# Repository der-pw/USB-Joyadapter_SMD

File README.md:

# USB-Joyadapter_SMD  
ATtiny basierter USB adapter für classic DB9 joysticks.

Die Ursprungsidee kommt aus dem forum64.de.  
https://www.forum64.de/index.php?thread/43055-usb-joystickadapter-neue-firmware-weiterentwicklung/

Die Software ist frei verfügbar und wird u.a. in dem [Thread](https://www.forum64.de/index.php?thread/43055-usb-joystickadapter-neue-firmware-weiterentwicklung/&postID=1390222#post1390222) zum Download angeboten, alle anderen Quellen, zumindest die, die ich gefunden habe, laufen ins Leere.
Daher stelle ich die Daten, der Vollständigkeit halber in dem Ordner [USB-Joystickadapter_THT](https://github.com/der-pw/USB-Joyadapter_SMD/tree/main/USB-Joystickadapter_THT) mit zur Verfügung. Darin enthalten sind sowohl die Software, zwei kompillierte Versionen, einmal für ATtiny2313 und ATtiny4313 und zusätzlich auch die Boarddaten der "alten" THT-Version.  
Ich bin aber nicht der Author!

Ich wollte eine SMD Version, möglichst kompakt aber noch gut zum Handlöten, haben.
Das Platinenlayout liegt als [KiCad-Projekt](https://github.com/der-pw/USB-Joyadapter_SMD/tree/main/kicad) vor. Exportierte Gerberdaten für Fertiger (bspw. [JLCPCB](https://jlcpcb.com/)) kann man ebenfalls [hier herunterladen](https://github.com/der-pw/USB-Joyadapter_SMD/raw/main/Joyadapter_SMD_gerber.zip).

### Programmierung
Ich habe das Hexfile mittels [AVRDUDESS](https://github.com/zkemble/AVRDUDESS) und einem ISP-Programmer auf den ATtiny geschrieben.
Die ISP-Schnittstelle wurde aus Platzgründen als SMD-Pads ausgeführt.
Eine Möglichkeit, man lötet Verbindungskabel zum Programmer an, ober man baut mit einer Buchsenleiste 6x1 RM2,54, 6 Pogo-Pins (P50-B1) und dem [Adapter](https://github.com/der-pw/USB-Joyadapter_SMD/blob/main/3D%20print/Pogo-Adapter.stl) eine Programmierklemme.
Da man das Teil prinzipiell nur einmal flashed und die Software ist m.E. ausentwickelt, kann man wohl eher kurz ein paar Kabel anlöten.

Die Fuses habe ich folgendermaßen gesetzt.  
**Low:** *0xCF*  
**High:** *0xDB*  
**Ext:** *0xFF*  
Fusecalc: https://www.engbedded.com/fusecalc/

### Gehäuse
Es gibt auch ein Gehäuse in der Variante mit den hochstehenden DB9-Buchsen.  
Zum Festschrauben beider Gehäusehälften wurden 2x12mm Linsenkopfschrauben verwendet.

Alternativ könnte man auch 90° gewinkelte DB9-Buchsen verwenden. Dann gucken die Kabel rechts und links aus dem Gehäuse heraus.
Ich wollte es erst einmal recht kompakt haben.
Vielleicht ergibt sich nochmal die Gelegenheit für ein Gehäuse mit 90° Buchsen.

### Teileliste:
https://www.reichelt.de/my/1803950  
Einige Teile sind (Stand 06.21) schwer zu bekommen.  

Ein großer **Dank** geht an das [forum64.de](https://www.forum64.de/) und seine hilfsbereiten Mitglieder. :thumbsup:

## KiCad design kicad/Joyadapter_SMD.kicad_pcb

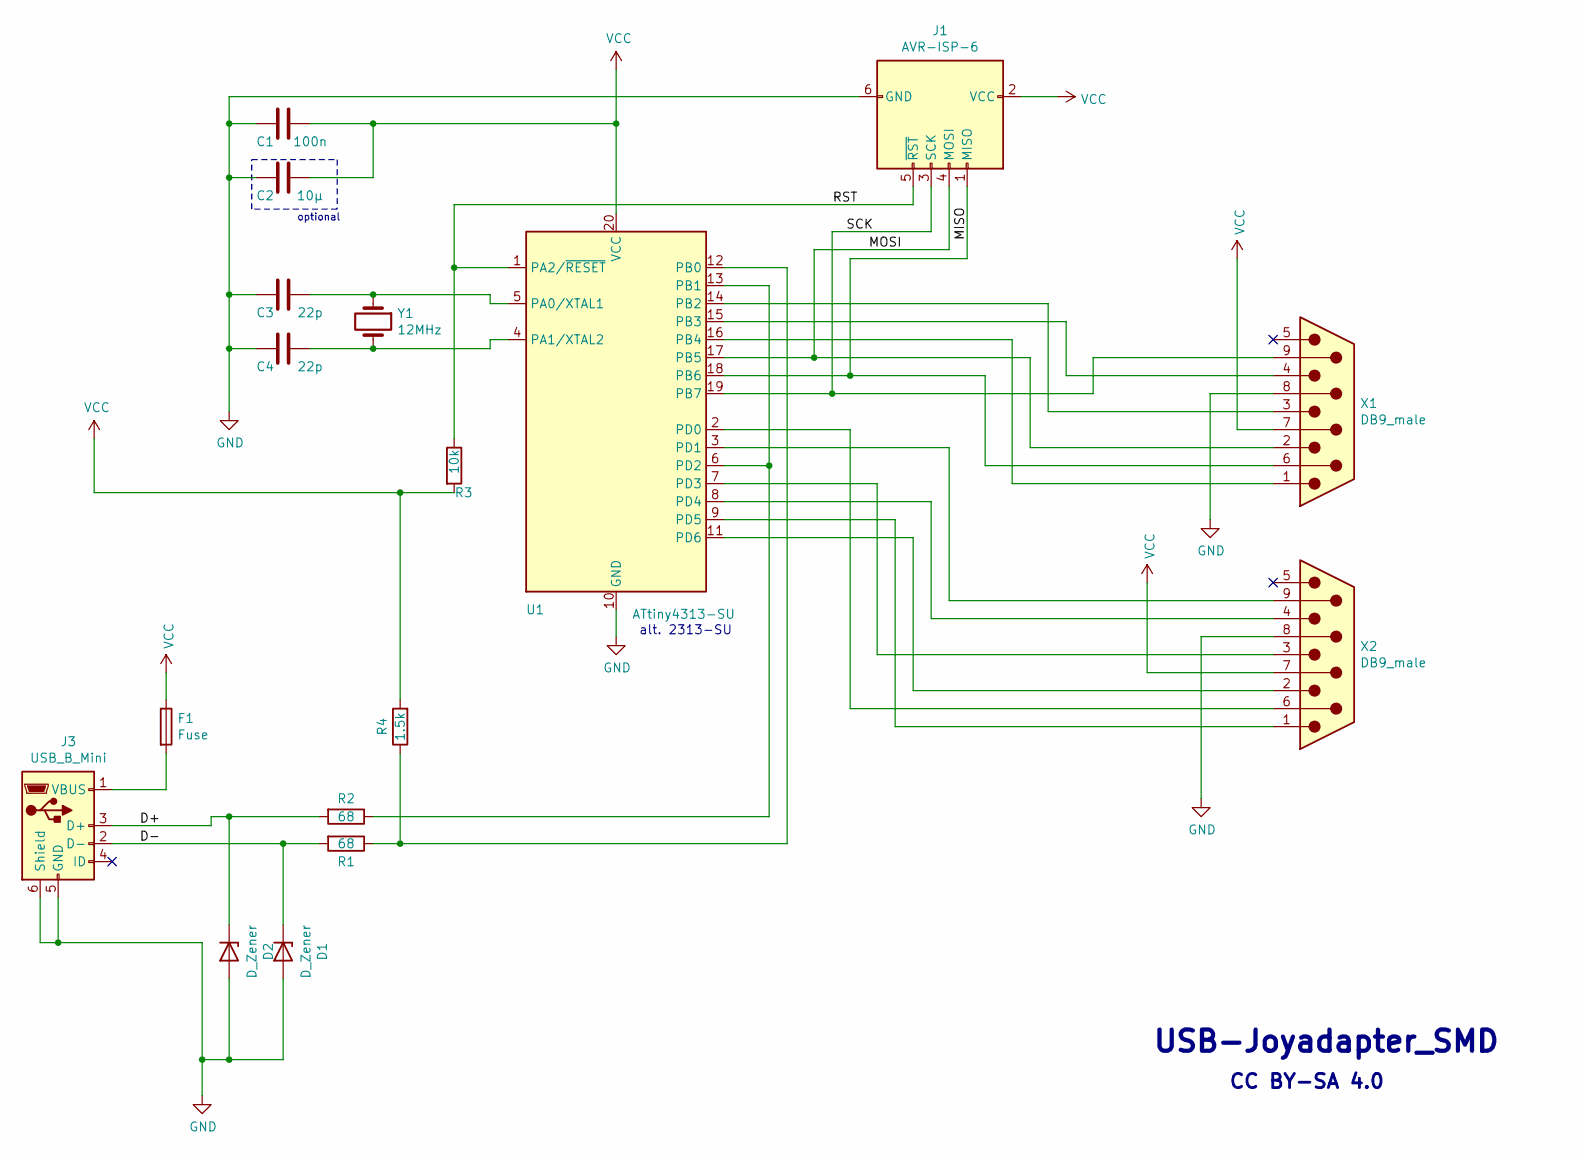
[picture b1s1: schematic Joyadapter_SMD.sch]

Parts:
C1: 100n; C_0805_2012Metric_Pad1.18x1.45mm_HandSolder
C2: 10µ; CP_EIA-3216-18_Kemet-A_Pad1.58x1.35mm_HandSolder
C3, C4: 22p; C_0805_2012Metric_Pad1.18x1.45mm_HandSolder
D1, D2: D_Zener; SOD-80
F1: Fuse; Fuse_0805_2012Metric_Pad1.15x1.40mm_HandSolder
J1: AVR-ISP-6; PinHeader_1x06_P2.54mm_Vertical
J3: USB_B_Mini; USB BWM USB-Einbaubuchse B-Mini
R1, R2: 68; R_0805_2012Metric_Pad1.20x1.40mm_HandSolder
R3: 10k; R_0805_2012Metric_Pad1.20x1.40mm_HandSolder
R4: 1.5k; R_0805_2012Metric_Pad1.20x1.40mm_HandSolder
U1: ATtiny4313-SU; SOIC-20W_7.5x12.8mm_P1.27mm
X1, X2: DB9_male; DSUB-9_Male_Vertical_P2.77x2.84mm_MountingHoles
Y1: 12MHz; HC49-SMD

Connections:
/D+: D2.1 (K), J3.3 (D+), R2.2
/D-: D1.1 (K), J3.2 (D-), R1.2
/MISO: J1.1 (MISO), U1.18 (PB6), X1.6
/MOSI: J1.4 (MOSI), U1.17 (PB5), X1.2
/RST: J1.5 (~RST), R3.1, U1.1 (PA2/~RESET)
/SCK: J1.3 (SCK), U1.19 (PB7), X1.9
GND: C1.2, C2.2, C3.2, C4.2, D1.2 (A), D2.2 (A), J1.6 (GND), J3.5 (GND), J3.6 (Shield), U1.10 (GND), X1.8, X2.8
unnamed: C3.1, U1.5 (PA0/XTAL1), Y1.1
unnamed: C4.1, U1.4 (PA1/XTAL2), Y1.2
unnamed: F1.2, J3.1 (VBUS)
unnamed: R1.1, R4.1, U1.12 (PB0)
unnamed: R2.1, U1.6 (PD2), U1.13 (PB1)
unnamed: U1.2 (PD0), X2.6
unnamed: U1.3 (PD1), X2.9
unnamed: U1.7 (PD3), X2.3
unnamed: U1.8 (PD4), X2.4
unnamed: U1.9 (PD5), X2.1
unnamed: U1.11 (PD6), X2.2
unnamed: U1.14 (PB2), X1.3
unnamed: U1.15 (PB3), X1.4
unnamed: U1.16 (PB4), X1.1
VCC: C1.1, C2.1, F1.1, J1.2 (VCC), R3.2, R4.2, U1.20 (VCC), X1.7, X2.7

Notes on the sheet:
alt. 2313-SU
optional
USB-Joyadapter_SMD
CC BY-SA 4.0

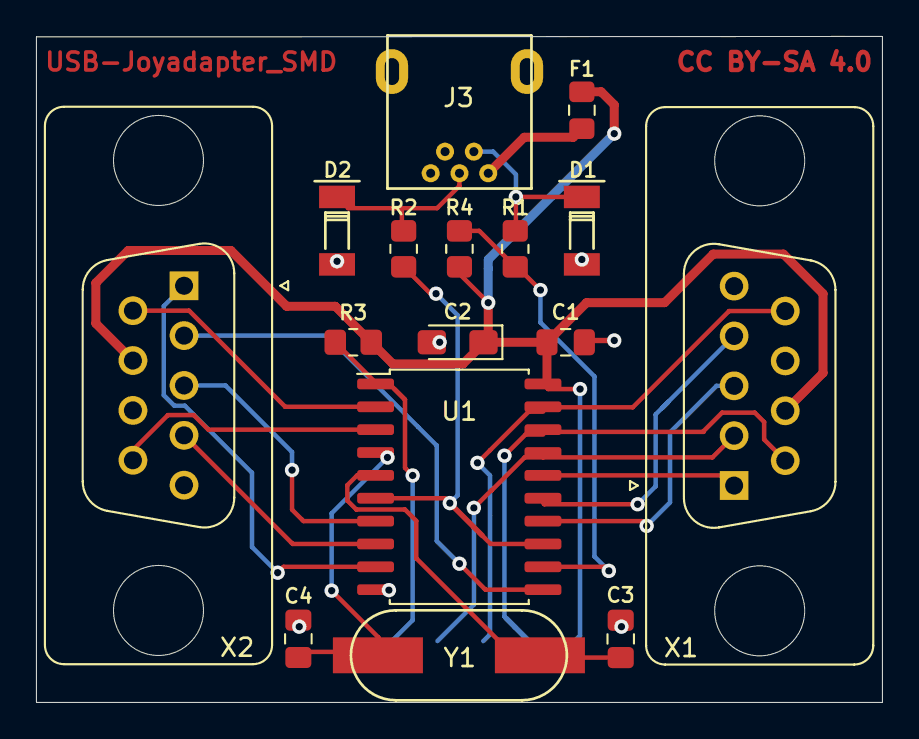
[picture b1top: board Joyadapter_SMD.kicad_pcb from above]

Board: 2 copper layers, 47.0 x 37.0 mm, 17 parts (1 on the bottom side), 22 nets.

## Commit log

2021-01-21 upload kicad Data
2021-02-03 Update
    Fuse added
2021-06-08 add picture
2021-06-08 Update README.md
    typos
2021-06-08 update pictures
2021-06-15 add schematic

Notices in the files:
README.md:
License: CC BY-SA 4.0
